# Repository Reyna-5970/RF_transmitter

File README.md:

# RF_transmitter
Arduino MEGA2560 to RPi 3B+ wireless communication for remote control of airplane

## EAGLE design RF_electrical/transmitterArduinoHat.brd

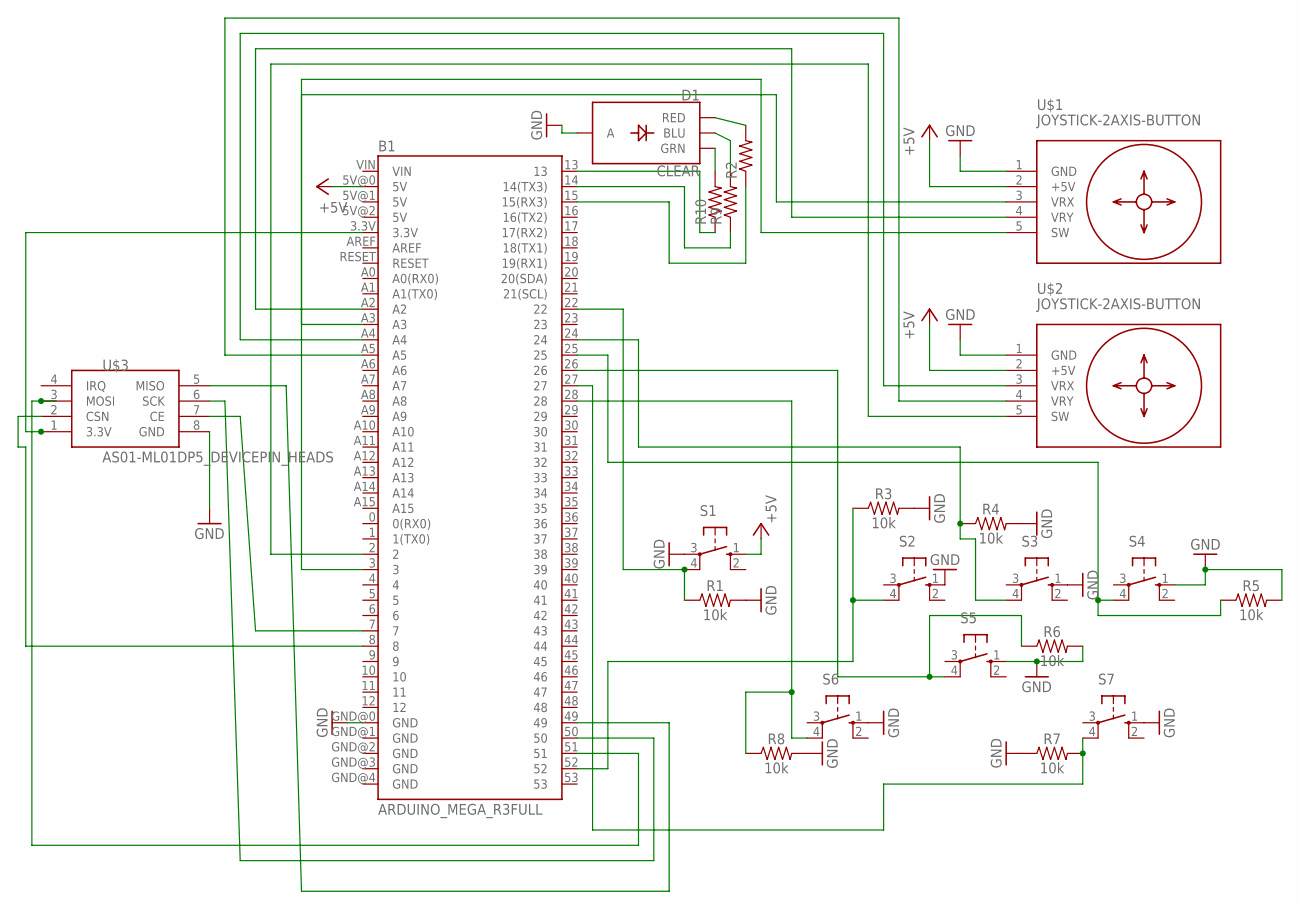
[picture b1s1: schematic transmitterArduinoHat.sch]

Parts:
B1: ARDUINO_MEGA_R3FULL; ARDUINO_MEGA
D1: CLEAR; LED-RGB-THRU
R1, R3, R4, R5, R6, R7, R8: 10k; AXIAL-0.1
R2, R9, R10: R-US_V234/12; V234/12
S1, S2, S3, S4, S5, S6, S7: 10-XX; B3F-10XX
U$1, U$2: JOYSTICK-2AXIS-BUTTON
U$3: AS01-ML01DP5_DEVICEPIN_HEADS; HDRV8W64P254_2X4_1016X508X838B

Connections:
+5V: B1.5V@0 (5V), S1.1 (S), U$1.2 (+5V), U$2.2 (+5V)
GND: B1.GND@0 (GND), D1.2 (A), R1.P$2 (2), R3.P$2 (2), R4.P$2 (2), R5.P$2 (2), R6.P$2 (2), R7.P$1 (1), R8.P$2 (2), S1.3, S2.1 (S), S3.1 (S), S4.1 (S), S5.1 (S), S6.1 (S), S7.1 (S), U$1.1 (GND), U$2.1 (GND), U$3.8 (GND)
unnamed: D1.4 (BLU), R9.2
unnamed: D1.1 (RED), R2.2
unnamed: B1.22, R1.P$1 (1), S1.4 (P1)
unnamed: B1.52, R3.P$1 (1), S2.4 (P1)
unnamed: D1.3 (GRN), R10.2
unnamed: B1.24, R4.P$1 (1), S3.4 (P1)
unnamed: B1.25, R5.P$1 (1), S4.4 (P1)
unnamed: B1.13, R10.1
unnamed: B1.14 (14(TX3)), R9.1
unnamed: B1.26, R6.P$1 (1), S5.4 (P1)
unnamed: B1.15 (15(RX3)), R2.1
unnamed: B1.27, R7.P$2 (2), S7.4 (P1)
unnamed: B1.28, R8.P$1 (1), S6.4 (P1)
unnamed: B1.3.3V, U$3.1 (3.3V)
unnamed: B1.3, U$1.5 (SW)
unnamed: B1.2, U$2.5 (SW)
unnamed: B1.A3, U$1.3 (VRX)
unnamed: B1.A2, U$1.4 (VRY)
unnamed: B1.A4, U$2.3 (VRX)
unnamed: B1.A5, U$2.4 (VRY)
unnamed: B1.8, U$3.2 (CSN)
unnamed: B1.7, U$3.7 (CE)
unnamed: B1.51, U$3.3 (MOSI)
unnamed: B1.50, U$3.6 (SCK)
unnamed: B1.49, U$3.5 (MISO)

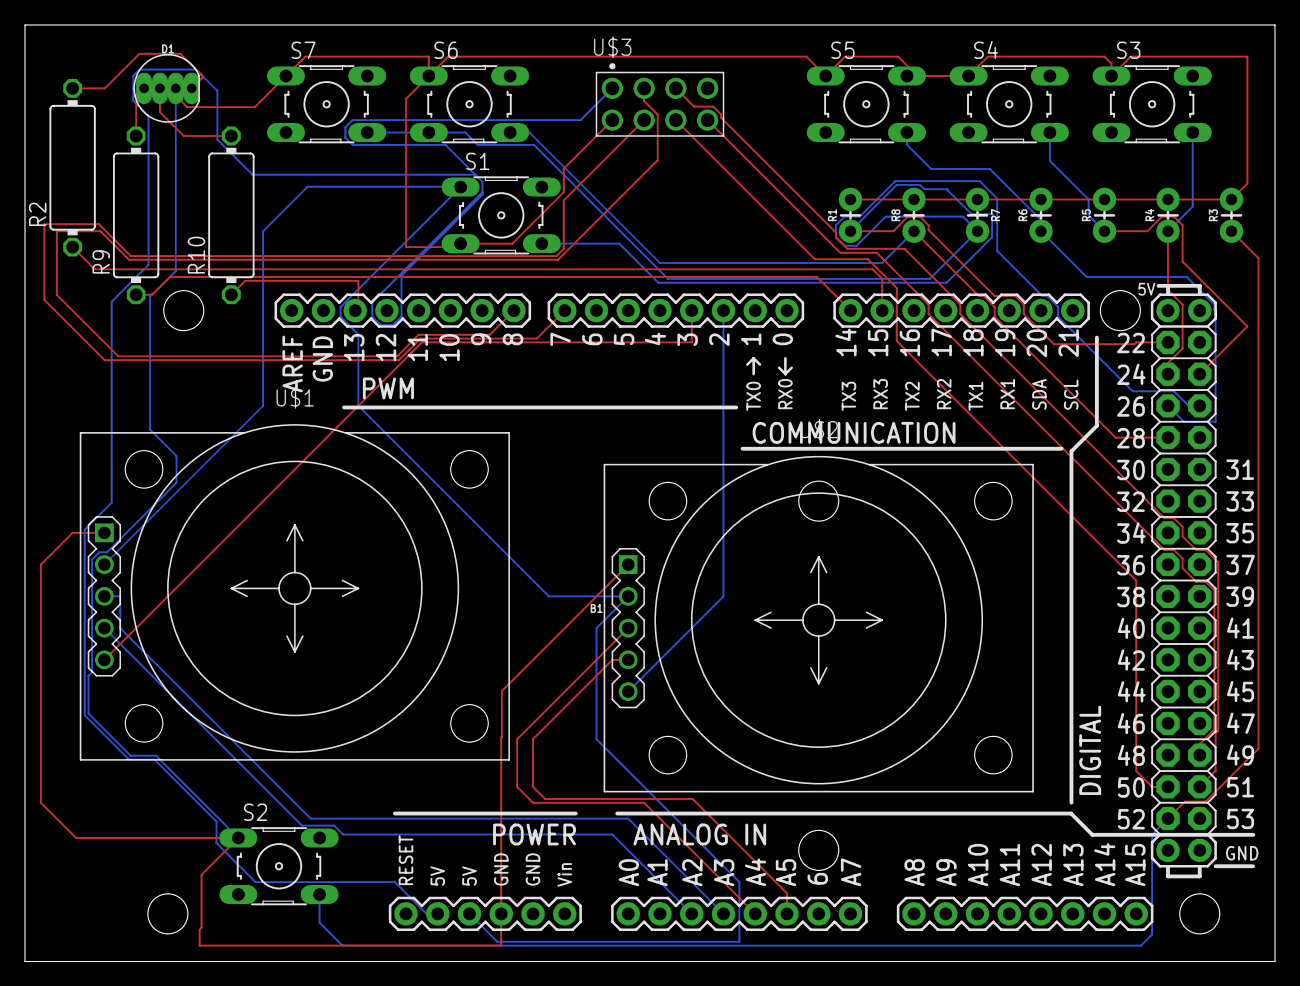
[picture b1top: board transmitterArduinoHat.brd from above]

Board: 2 copper layers, 100.0 x 74.9 mm, 22 parts (0 on the bottom side), 27 nets.

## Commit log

2020-06-25 Mechanical CAD of bottom and top pieces to transmitter -- without buttons
2020-06-25 Rough electrical schematic for Arduino shield
    Will likely add pressure sensor
2020-06-27 Changed status light to RGB and modified resistors
2020-06-27 Successful trials of button and joystick serial monitor response. Untested transmitter
2020-06-28 Documented wiring. Created directory
2020-06-29 Added RF device to schematic & PCB. Starting to create prototype cpp program on Arduino.
2020-06-29 First version of cpp program. Fixed refs (don't put libs in git repos)
2020-06-30 Fixed library issue
    https://www.arduino.cc/en/guide/libraries
2020-06-30 Annotated with comments
2020-10-02 Fixed GND connection in PCB. Revised code, ready for LED testing once PCB is ready.

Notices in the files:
parts and their libraries:
SparkFun-Resistors: Licensing: Creative Commons ShareAlike 4.0 International - https://creativecommons.org/licenses/by-sa/4.0
joystick: Released under the Creative Commons Attribution 4.0 International License: http://creativecommons.org/licenses/by/4.0
